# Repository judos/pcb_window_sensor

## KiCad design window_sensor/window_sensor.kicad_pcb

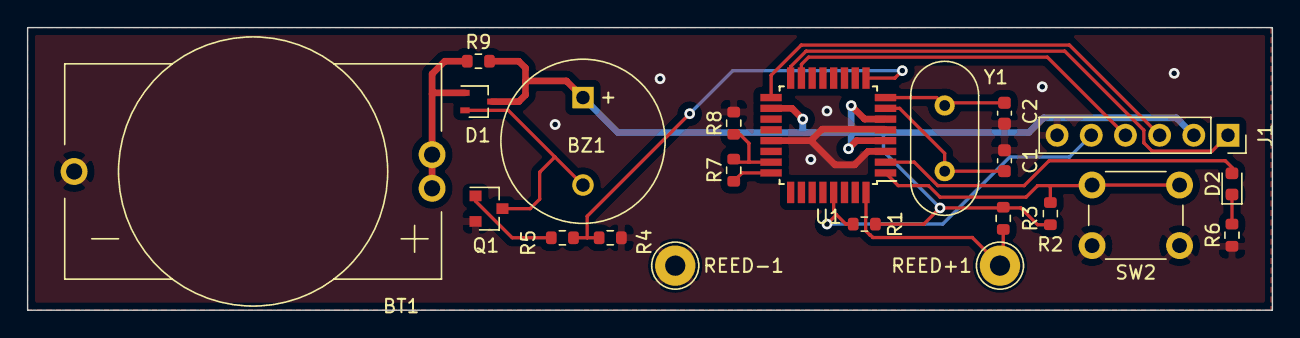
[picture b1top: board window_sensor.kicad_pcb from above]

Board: 2 copper layers, 92.5 x 21.0 mm, 22 parts (0 on the bottom side), 18 nets.

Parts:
BT1: Battery_Cell; RND_305-00032_CR2032_Holder
BZ1: Buzzer; MagneticBuzzer_ProSignal_ABT-410-RC
C1, C2: 10pF; C_0603_1608Metric
D1: BAT54CW; SOT-323_SC-70
D2: LED; LED_0603_1608Metric
J1: AVR-ISP-6; PinSocket_1x06_P2.54mm_Vertical
Q1: 2N7002; SOT-23
R1, R5: 10k; R_0603_1608Metric
R2, R3, R4, R7, R8: 100k; R_0603_1608Metric
R6: 120R; R_0603_1608Metric
R9: 0R; R_0603_1608Metric
REED+1: TestPoint; TestPoint_THTPad_D3.0mm_Drill1.5mm
REED-1: TestPoint; TestPoint_THTPad_D3.0mm_Drill1.5mm
SW2: SW_Push; SW_PUSH_6mm_H4.3mm
U1: ATmega328P-AU; TQFP-32_7x7mm_P0.8mm
Y1: 4MHz; Crystal_HC49-4H_Vertical

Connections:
/ADC/VIN: R7.1, U1.24
/ADC/VOUT: R7.2, R8.1, U1.23
/I/O/BUZZER: R4.2, R5.2, U1.9
/I/O/Button: R2.2, SW2.2, U1.1
/I/O/LED: D2.2, U1.2
/I/O/SPEAKER-: BZ1.2, D1.2, Q1.3
/I/O/Sensor: R3.2, REED+1.1, U1.32
/oscillator/XTAL_1: C1.2, U1.7, Y1.2
/oscillator/XTAL_2: C2.2, U1.8, Y1.1
GND: BT1.2, C1.1, C2.1, J1.6, Q1.2, R4.1, R6.1, R8.2, REED-1.1, SW2.1, U1.3, U1.5, U1.21
MISO: J1.1, U1.16
MOSI: J1.4, U1.15
unnamed: D2.1, R6.2
unnamed: Q1.1, R5.1
SCK: J1.3, U1.17
VBAT: BT1.1, D1.1, R9.1
VCC: BZ1.1, D1.3, J1.2, R1.1, R2.1, R3.1, R9.2, U1.4, U1.6, U1.18
~RESET: J1.5, R1.2, U1.29
